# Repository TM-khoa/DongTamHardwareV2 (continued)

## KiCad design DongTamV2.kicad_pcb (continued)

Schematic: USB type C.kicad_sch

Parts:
C26: 100nF; C_0805
C27: 1uF Tantalum; CP_EIA-3216-10_Kemet-I
J12: USB_C_Receptacle; USB_C_Receptacle_XKB_U262-16XN-4BVC11
R51, R52: 5k1; R_0603
R53: 1k5; R_0603
U9: USBLC6-2SC6; SOT-23-6

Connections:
+3.3V: R53.2; also elsewhere on the board
/STM32/USB_DM: J12.A7 (D-), J12.B7 (D-), U9.1 (I/O1), U9.6 (I/O1); also elsewhere on the board
/STM32/USB_DP: J12.A6 (D+), J12.B6 (D+), R53.1, U9.3 (I/O2), U9.4 (I/O2); also elsewhere on the board
/VBUS: C26.1, C27.1, J12.A4 (VBUS), J12.A9 (VBUS), J12.B4 (VBUS), J12.B9 (VBUS), U9.5 (VBUS); also elsewhere on the board
GND: C26.2, C27.2, J12.A1 (GND), J12.A12 (GND), J12.B1 (GND), J12.B12 (GND), J12.S1 (SHIELD), R51.2, R52.2, U9.2 (GND); also elsewhere on the board
unnamed: J12.A5 (CC1), R51.1
unnamed: J12.B5 (CC2), R52.1

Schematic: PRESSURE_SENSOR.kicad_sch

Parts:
C23: 100nF; C_0603
U6: AMS5915; Sensor-Pressure-AMS5915

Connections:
+5V: C23.2, U6.2 (VCC); also elsewhere on the board
/AMS5915/i2c.SCL: U6.4 (SCL); also elsewhere on the board
/AMS5915/i2c.SDA: U6.3 (SDA); also elsewhere on the board
GND: C23.1, U6.1 (GND); also elsewhere on the board

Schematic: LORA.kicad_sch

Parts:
C41: 100nF; C_0805
U17: RF_Module_Ai-Thinker-Ra-02; Module-LORA-RA02

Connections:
+3.3V: C41.1, U17.3 (VDD); also elsewhere on the board
/LORA/LoRaReceivedInterrupt: U17.5 (DIO0); also elsewhere on the board
/LORA/LoRaReset: U17.4 (~RESET)
/LORA/RA02.CS_LORA: U17.15 (~NSS); also elsewhere on the board
/LORA/RA02.MISO: U17.13 (MISO); also elsewhere on the board
/LORA/RA02.MOSI: U17.14 (MOSI); also elsewhere on the board
/LORA/RA02.SCK: U17.12 (SCK); also elsewhere on the board
GND: C41.2, U17.1 (GND), U17.2 (GND), U17.9 (GND), U17.16 (GND); also elsewhere on the board

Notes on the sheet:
Chú ý antenna phải cách xa tín hiệu nhạy nên đặt gần cạnh board

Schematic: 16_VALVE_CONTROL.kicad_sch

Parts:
C24, C25: 100nF; C_0603
LE3, LE4, LE5, LE6, LE7, LE8, LE9, LE10, LE11, LE12, LE13, LE14, LE15, LE16, LE17, LE18: Blue 0603; LED_0603
R25, R26, R27, R28, R29, R30, R31, R32, R33, R34, R35, R36, R37, R38, R39, R40: 1k; R_0603
U7, U8: 74HC595; Package-IC-Vert-SMD-1.27mm-16P-SOIC_16_Narrow_3.92x10.2mm

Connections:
+5V: C24.2, C25.2, U7.10 (~SRCLR), U7.16 (VCC), U8.10 (~SRCLR), U8.16 (VCC); also elsewhere on the board
/16ValveDriver/ValveDriver1: R25.1, U7.15 (QA); also elsewhere on the board
/16ValveDriver/ValveDriver2: R26.1, U7.1 (QB); also elsewhere on the board
/16ValveDriver/ValveDriver3: R27.1, U7.2 (QC); also elsewhere on the board
/16ValveDriver/ValveDriver4: R28.1, U7.3 (QD); also elsewhere on the board
/16ValveDriver/ValveDriver5: R29.1, U7.4 (QE); also elsewhere on the board
/16ValveDriver/ValveDriver6: R30.1, U7.5 (QF); also elsewhere on the board
/16ValveDriver/ValveDriver7: R31.1, U7.6 (QG); also elsewhere on the board
/16ValveDriver/ValveDriver8: R32.1, U7.7 (QH); also elsewhere on the board
/16ValveDriver/ValveDriver9: R33.1, U8.15 (QA); also elsewhere on the board
/16ValveDriver/ValveDriver10: R34.1, U8.1 (QB); also elsewhere on the board
/16ValveDriver/ValveDriver11: R35.1, U8.2 (QC); also elsewhere on the board
/16ValveDriver/ValveDriver12: R36.1, U8.3 (QD); also elsewhere on the board
/16ValveDriver/ValveDriver13: R37.1, U8.4 (QE); also elsewhere on the board
/16ValveDriver/ValveDriver14: R38.1, U8.5 (QF); also elsewhere on the board
/16ValveDriver/ValveDriver15: R39.1, U8.6 (QG); also elsewhere on the board
/16ValveDriver/ValveDriver16: R40.1, U8.7 (QH); also elsewhere on the board
/ReadValveState/OE: U7.13 (~OE), U8.13 (~OE); also elsewhere on the board
/STM32/595.RCLK: U7.12 (RCLK), U8.12 (RCLK); also elsewhere on the board
/STM32/595.SER: U7.14 (SER); also elsewhere on the board
/STM32/595.SRCLK: U7.11 (SRCLK), U8.11 (SRCLK); also elsewhere on the board
GND: C24.1, C25.1, LE3.2, LE4.2, LE5.2, LE6.2, LE7.2, LE8.2, LE9.2, LE10.2, LE11.2, LE12.2, LE13.2, LE14.2, LE15.2, LE16.2, LE17.2, LE18.2, U7.8 (GND), U8.8 (GND); also elsewhere on the board
unnamed: LE3.1, R25.2
unnamed: LE4.1, R26.2
unnamed: LE5.1, R27.2
unnamed: LE6.1, R28.2
unnamed: LE7.1, R29.2
unnamed: LE8.1, R30.2
unnamed: LE9.1, R31.2
unnamed: LE10.1, R32.2
unnamed: LE11.1, R33.2
unnamed: LE12.1, R34.2
unnamed: LE13.1, R35.2
unnamed: LE14.1, R36.2
unnamed: LE15.1, R37.2
unnamed: LE16.1, R38.2
unnamed: LE17.1, R39.2
unnamed: LE18.1, R40.2
unnamed: U7.9 (QH'), U8.14 (SER)

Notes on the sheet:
74HC595
LED INDICATOR

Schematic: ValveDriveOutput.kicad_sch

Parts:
C32: 100nF; C_0603
D9, D10, D11, D12: 1N4148W; Package-Diode-D_SOD_323
J13: KF-5.08-8-V; TerminalBlock-Horz-THT-8P-P5.08mm-KF2EDG_Pluggable
Q6, Q7, Q8, Q9: SI2302; SOT23-3
R54, R55, R56, R57: 1M; R_0603
R58, R59, R60, R61: 0R5; R_0805_2012Metric
R62, R63, R64, R65: 1k; R_0603
U11: LM324; Package-IC-Vert-SMD-1.27mm-14P-SOIC_14_Narrow_3.9x8.7mm

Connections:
+24V: D9.2, D10.2, D11.2, D12.2, J13.1, J13.3, J13.5, J13.7; also elsewhere on the board
/16ValveDriver/4ValveDriveOutput/VAN1-: D9.1, J13.2, Q6.3 (D)
/16ValveDriver/4ValveDriveOutput/VAN2-: D10.1, J13.4, Q7.3 (D)
/16ValveDriver/4ValveDriveOutput/VAN3-: D11.1, J13.6, Q8.3 (D)
/16ValveDriver/4ValveDriveOutput/VAN4-: D12.1, J13.8, Q9.3 (D)
/16ValveDriver/AnalogVCC: C32.1, R62.1, R63.1, R64.1, R65.1, U11.4 (V+); also elsewhere on the board
/16ValveDriver/OpAmpOutput1: R62.2, U11.7; also elsewhere on the board
/16ValveDriver/OpAmpOutput2: R63.2, U11.1; also elsewhere on the board
/16ValveDriver/OpAmpOutput3: R64.2, U11.14; also elsewhere on the board
/16ValveDriver/OpAmpOutput4: R65.2, U11.8; also elsewhere on the board
/16ValveDriver/REF: U11.2 (-), U11.6 (-), U11.9 (-), U11.13 (-); also elsewhere on the board
/16ValveDriver/ValveDriver1: Q6.1 (G), R54.1; also elsewhere on the board
/16ValveDriver/ValveDriver2: Q7.1 (G), R55.1; also elsewhere on the board
/16ValveDriver/ValveDriver3: Q8.1 (G), R56.1; also elsewhere on the board
/16ValveDriver/ValveDriver4: Q9.1 (G), R57.1; also elsewhere on the board
GND: R54.2, R55.2, R56.2, R57.2, R58.2, R59.2, R60.2, R61.2; also elsewhere on the board
GNDA: C32.2, U11.11 (V-); also elsewhere on the board
unnamed: Q6.2 (S), R58.1, U11.5 (+)
unnamed: Q7.2 (S), R59.1, U11.3 (+)
unnamed: Q8.2 (S), R60.1, U11.12 (+)
unnamed: Q9.2 (S), R61.1, U11.10 (+)

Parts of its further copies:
C33, C34, C35: 100nF; C_0603
D13, D14, D15, D16, D17, D18, D19, D20, D21, D22, D23, D24: 1N4148W; Package-Diode-D_SOD_323
J14, J15, J16: KF-5.08-8-V; TerminalBlock-Horz-THT-8P-P5.08mm-KF2EDG_Pluggable
Q10, Q11, Q12, Q13, Q14, Q15, Q16, Q17, Q18, Q19, Q20, Q21: SI2302; SOT23-3
R66, R67, R68, R69, R78, R79, R80, R81, R90, R91, R92, R93: 1M; R_0603
R70, R71, R72, R73, R82, R83, R84, R85, R94, R95, R96, R97: 0R5; R_0805_2012Metric
R74, R75, R76, R77, R86, R87, R88, R89, R98, R99, R100, R101: 1k; R_0603
U12, U13, U14: LM324; Package-IC-Vert-SMD-1.27mm-14P-SOIC_14_Narrow_3.9x8.7mm

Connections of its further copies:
+24V: D13.2, D14.2, D15.2, D16.2, D17.2, D18.2, D19.2, D20.2, D21.2, D22.2, D23.2, D24.2, J14.1, J14.3, J14.5, J14.7, J15.1, J15.3, J15.5, J15.7, J16.1, J16.3, J16.5, J16.7; also elsewhere on the board
/16ValveDriver/4ValveDriveOutput1/VAN1-: D13.1, J14.2, Q10.3 (D)
/16ValveDriver/4ValveDriveOutput1/VAN2-: D14.1, J14.4, Q11.3 (D)
/16ValveDriver/4ValveDriveOutput1/VAN3-: D15.1, J14.6, Q12.3 (D)
/16ValveDriver/4ValveDriveOutput1/VAN4-: D16.1, J14.8, Q13.3 (D)
/16ValveDriver/4ValveDriveOutput2/VAN1-: D17.1, J15.2, Q14.3 (D)
/16ValveDriver/4ValveDriveOutput2/VAN2-: D18.1, J15.4, Q15.3 (D)
/16ValveDriver/4ValveDriveOutput2/VAN3-: D19.1, J15.6, Q16.3 (D)
/16ValveDriver/4ValveDriveOutput2/VAN4-: D20.1, J15.8, Q17.3 (D)
/16ValveDriver/4ValveDriveOutput3/VAN1-: D21.1, J16.2, Q18.3 (D)
/16ValveDriver/4ValveDriveOutput3/VAN2-: D22.1, J16.4, Q19.3 (D)
/16ValveDriver/4ValveDriveOutput3/VAN3-: D23.1, J16.6, Q20.3 (D)
/16ValveDriver/4ValveDriveOutput3/VAN4-: D24.1, J16.8, Q21.3 (D)
/16ValveDriver/AnalogVCC: C33.1, C34.1, C35.1, R74.1, R75.1, R76.1, R77.1, R86.1, R87.1, R88.1, R89.1, R98.1, R99.1, R100.1, R101.1, U12.4 (V+), U13.4 (V+), U14.4 (V+); also elsewhere on the board
/16ValveDriver/OpAmpOutput5: R74.2, U12.7; also elsewhere on the board
/16ValveDriver/OpAmpOutput6: R75.2, U12.1; also elsewhere on the board
/16ValveDriver/OpAmpOutput7: R76.2, U12.14; also elsewhere on the board
/16ValveDriver/OpAmpOutput8: R77.2, U12.8; also elsewhere on the board
/16ValveDriver/OpAmpOutput9: R86.2, U13.7; also elsewhere on the board
/16ValveDriver/OpAmpOutput10: R87.2, U13.1; also elsewhere on the board
/16ValveDriver/OpAmpOutput11: R88.2, U13.14; also elsewhere on the board
/16ValveDriver/OpAmpOutput12: R89.2, U13.8; also elsewhere on the board
/16ValveDriver/OpAmpOutput13: R98.2, U14.7; also elsewhere on the board
/16ValveDriver/OpAmpOutput14: R99.2, U14.1; also elsewhere on the board
/16ValveDriver/OpAmpOutput15: R100.2, U14.14; also elsewhere on the board
/16ValveDriver/OpAmpOutput16: R101.2, U14.8; also elsewhere on the board
/16ValveDriver/REF: U12.2 (-), U12.6 (-), U12.9 (-), U12.13 (-), U13.2 (-), U13.6 (-), U13.9 (-), U13.13 (-), U14.2 (-), U14.6 (-), U14.9 (-), U14.13 (-); also elsewhere on the board
/16ValveDriver/ValveDriver5: Q10.1 (G), R66.1; also elsewhere on the board
/16ValveDriver/ValveDriver6: Q11.1 (G), R67.1; also elsewhere on the board
/16ValveDriver/ValveDriver7: Q12.1 (G), R68.1; also elsewhere on the board
/16ValveDriver/ValveDriver8: Q13.1 (G), R69.1; also elsewhere on the board
/16ValveDriver/ValveDriver9: Q14.1 (G), R78.1; also elsewhere on the board
/16ValveDriver/ValveDriver10: Q15.1 (G), R79.1; also elsewhere on the board
/16ValveDriver/ValveDriver11: Q16.1 (G), R80.1; also elsewhere on the board
/16ValveDriver/ValveDriver12: Q17.1 (G), R81.1; also elsewhere on the board
/16ValveDriver/ValveDriver13: Q18.1 (G), R90.1; also elsewhere on the board
/16ValveDriver/ValveDriver14: Q19.1 (G), R91.1; also elsewhere on the board
/16ValveDriver/ValveDriver15: Q20.1 (G), R92.1; also elsewhere on the board
/16ValveDriver/ValveDriver16: Q21.1 (G), R93.1; also elsewhere on the board
GND: R66.2, R67.2, R68.2, R69.2, R70.2, R71.2, R72.2, R73.2, R78.2, R79.2, R80.2, R81.2, R82.2, R83.2, R84.2, R85.2, R90.2, R91.2, R92.2, R93.2, R94.2, R95.2, R96.2, R97.2; also elsewhere on the board
GNDA: C33.2, C34.2, C35.2, U12.11 (V-), U13.11 (V-), U14.11 (V-); also elsewhere on the board
unnamed: Q10.2 (S), R70.1, U12.5 (+)
unnamed: Q11.2 (S), R71.1, U12.3 (+)
unnamed: Q12.2 (S), R72.1, U12.12 (+)
unnamed: Q13.2 (S), R73.1, U12.10 (+)
unnamed: Q14.2 (S), R82.1, U13.5 (+)
unnamed: Q15.2 (S), R83.1, U13.3 (+)
unnamed: Q16.2 (S), R84.1, U13.12 (+)
unnamed: Q17.2 (S), R85.1, U13.10 (+)
unnamed: Q18.2 (S), R94.1, U14.5 (+)
unnamed: Q19.2 (S), R95.1, U14.3 (+)
unnamed: Q20.2 (S), R96.1, U14.12 (+)
unnamed: Q21.2 (S), R97.1, U14.10 (+)

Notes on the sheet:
Thực nghiệm hoạt động của TL084 không khả thi để lấy mẫu điện áp từ van kích, chọn LM324 thay thế

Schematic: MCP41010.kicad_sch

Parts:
C40: 100nF; C_0603
R118, R119: 0; R_0603
U21: MCP41010; Package-IC-Vert-SMD-1.27mm-8P-SOIC_8_Narrow_3.9x4.9mm

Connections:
+5V: C40.1, R118.1, U21.8 (VDD); also elsewhere on the board
/16ValveDriver/AnalogVCC: R118.2, U21.5 (PA0); also elsewhere on the board
/16ValveDriver/REF: U21.6 (PW0); also elsewhere on the board
/LORA/RA02.CS_MCP41010: U21.1 (~CS); also elsewhere on the board
/LORA/RA02.MOSI: U21.3 (SI); also elsewhere on the board
/LORA/RA02.SCK: U21.2 (SCK); also elsewhere on the board
GND: C40.2, R119.1, U21.4 (VSS); also elsewhere on the board
GNDA: R119.2, U21.7 (PB0); also elsewhere on the board

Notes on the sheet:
High Frequency
Giảm thiếu tiếp xúc giữa vùng digital và analog, cần phải hàn trở này để cấp nguồn
Digital and analog traces should be separated as much as possible on the board, with no traces running underneath the device or the bypass capacitor High-frequency signals (such as clock lines) keep as far as possible from analog traces. Use of an analog ground plane is recommended in order to keep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
MCP41010

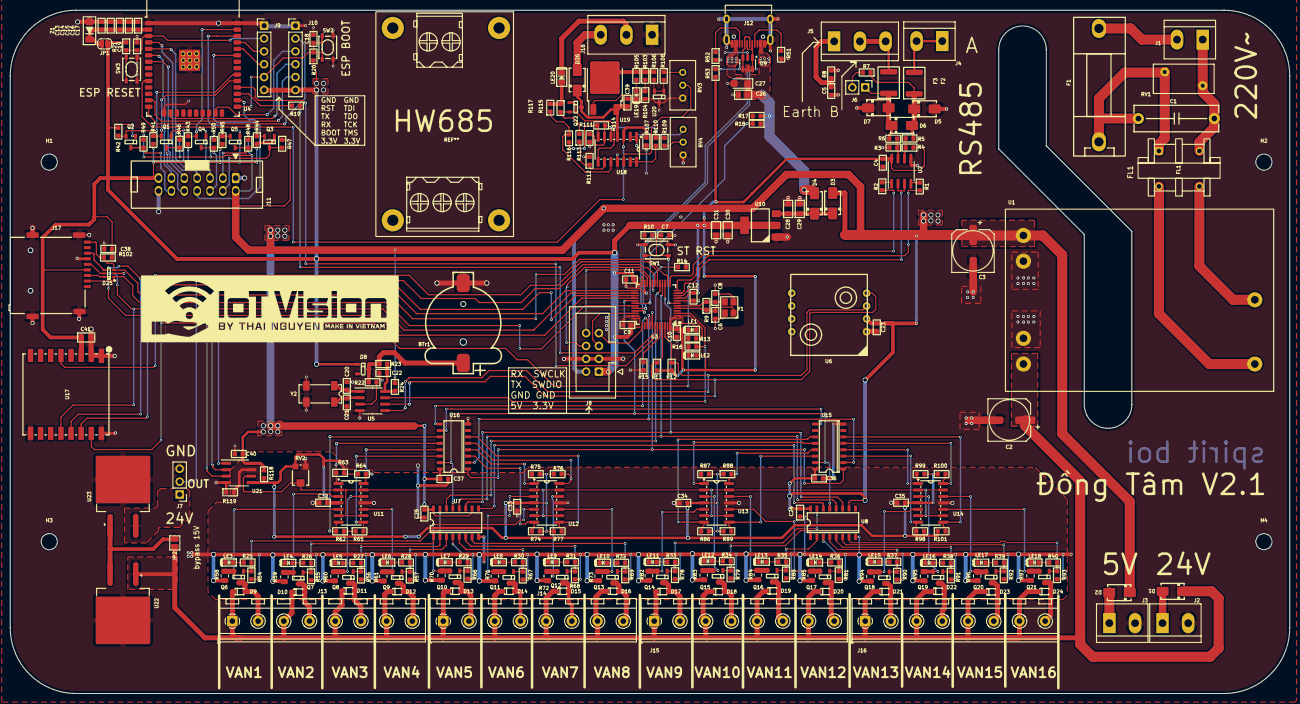
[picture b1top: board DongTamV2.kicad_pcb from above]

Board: 2 copper layers, 252.8 x 135.0 mm, 290 parts (0 on the bottom side), 202 nets.

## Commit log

2024-02-27 Rebuild schematic to new version, add USB periph, fix bug
2024-02-29 finish some unconnect pins, draw edge cut board
2024-02-29 Add LORA, SDcard and Volt to 4_20mA scheamtic
2024-02-29 remove old schem files
2024-02-29 Add README, Lora received interrupt pin
    Change LED pin from PB0 to PC13, PCF8563_CLKOUT to PC14
    PB0 add Lora received interrupt pin
2024-03-09 Feat: Components's layout
2024-03-09 fix board dimension and add module HW685
2024-03-13 Fix & Update: ESP32 and STM32 layout
2024-03-19 fix: Size of board and position of components
2024-03-20 Complete to pull
2024-03-20 feat <Wiring>: Complete wiring for power, RS485 and USB
2024-04-03 fix board edge cut
2024-04-03 layout p1
2024-04-03 Layout p2, fix Analog VCC and GND for opamp circuit
2024-04-04 Complete layout, HW685 not layout yet
2024-05-24 fix: name 1N4007 to 1N4148W
2024-05-24 feat: Add pullup resistor PCF8563_CLKOUT pin
2024-08-13 feat: adding HW685 module
2024-08-13 Update hardware README
